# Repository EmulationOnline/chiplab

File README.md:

# Chiplab by EmulationOnline

The Chiplab is a research platform for studying the behavior of (initially just digital)
integrated circuits. 

More information about motivation & history can be found at:

https://emulationonline.com/systems/chiplab

## Structure

The long term vision is that there will be significant reuse or at least
similarity across chips, so this project is structured as a monorepo.

For a given chip supported in the lab, there are several relevant pieces:
- target. Programs meant to run on the microcontroller.
- firmware. This code runs on a microcontroller and interfaces with the 
target IC. Its core functionality is to set and read the pins
on the target IC.
- host. This is code that runs on a more powerful machine, and communicates
with the firmware program over serial.
- board. This is the electronics design for a board containing the
microcontroller, the target IC, and a serial interface for communicating
with the host.

For the 6502 chip, for example, code lives in the following folders:
- 6502/target
- 6502/firmware
- 6502/host
- 6502/board

## Contributing

If you see an issue, feel free to either open a Github issue. Please open an
issue before sending a pull request, so we can discuss. This helps make sure
we're on the same page and reduce time to implement fixes.

If you would like to see a new chip covered, feel free to open an issue. Since
supporting a chip requires several pieces, a good way to achieve this is to
build a prototype yourself by forking the 6502 code, and sending a pull request
once things are working.

## Consider donating

Donations are a great way of contributing. Funds are used both to fund
development and to acquire the hardware to add to the lab.

https://ko-fi.com/emulationonline

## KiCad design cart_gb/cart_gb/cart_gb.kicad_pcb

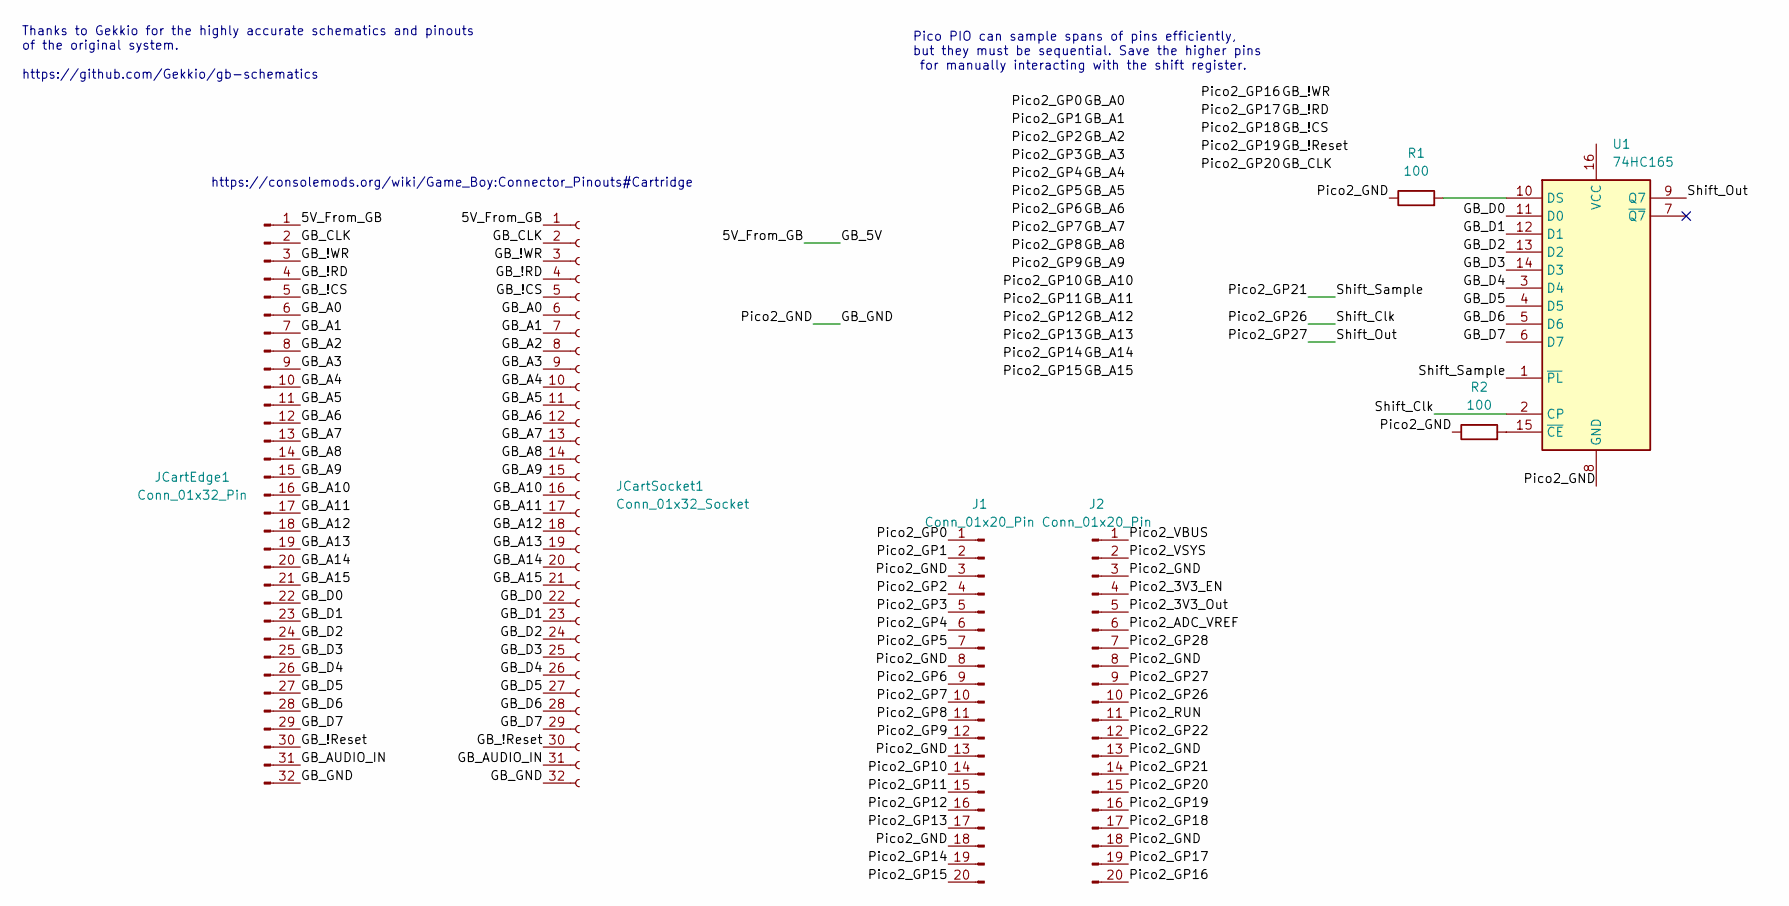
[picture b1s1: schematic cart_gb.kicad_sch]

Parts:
J1, J2: Conn_01x20_Pin; PinHeader_1x20_P2.54mm_Vertical
JCartEdge1: Conn_01x32_Pin; GameBoy_GamePak_DMG-09_P1.50mm_Edge
JCartSocket1: Conn_01x32_Socket; GameBoy_Cartridge_DMG_1x32_P1.50mm_Socket_Horizontal
R1, R2: 100; R_Axial_DIN0204_L3.6mm_D1.6mm_P1.90mm_Vertical
U1: 74HC165; DIP-16_W7.62mm_Socket

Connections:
/5V_From_GB: JCartEdge1.1, JCartSocket1.1
/GB_!CS: J2.17, JCartEdge1.5, JCartSocket1.5
/GB_!RD: J2.19, JCartEdge1.4, JCartSocket1.4
/GB_!Reset: J2.16, JCartEdge1.30, JCartSocket1.30
/GB_!WR: J2.20, JCartEdge1.3, JCartSocket1.3
/GB_A0: J1.1, JCartEdge1.6, JCartSocket1.6
/GB_A1: J1.2, JCartEdge1.7, JCartSocket1.7
/GB_A2: J1.4, JCartEdge1.8, JCartSocket1.8
/GB_A3: J1.5, JCartEdge1.9, JCartSocket1.9
/GB_A4: J1.6, JCartEdge1.10, JCartSocket1.10
/GB_A5: J1.7, JCartEdge1.11, JCartSocket1.11
/GB_A6: J1.9, JCartEdge1.12, JCartSocket1.12
/GB_A7: J1.10, JCartEdge1.13, JCartSocket1.13
/GB_A8: J1.11, JCartEdge1.14, JCartSocket1.14
/GB_A9: J1.12, JCartEdge1.15, JCartSocket1.15
/GB_A10: J1.14, JCartEdge1.16, JCartSocket1.16
/GB_A11: J1.15, JCartEdge1.17, JCartSocket1.17
/GB_A12: J1.16, JCartEdge1.18, JCartSocket1.18
/GB_A13: J1.17, JCartEdge1.19, JCartSocket1.19
/GB_A14: J1.19, JCartEdge1.20, JCartSocket1.20
/GB_A15: J1.20, JCartEdge1.21, JCartSocket1.21
/GB_AUDIO_IN: JCartEdge1.31, JCartSocket1.31
/GB_CLK: J2.15, JCartEdge1.2, JCartSocket1.2
/GB_D0: JCartEdge1.22, JCartSocket1.22, U1.11 (D0)
/GB_D1: JCartEdge1.23, JCartSocket1.23, U1.12 (D1)
/GB_D2: JCartEdge1.24, JCartSocket1.24, U1.13 (D2)
/GB_D3: JCartEdge1.25, JCartSocket1.25, U1.14 (D3)
/GB_D4: JCartEdge1.26, JCartSocket1.26, U1.3 (D4)
/GB_D5: JCartEdge1.27, JCartSocket1.27, U1.4 (D5)
/GB_D6: JCartEdge1.28, JCartSocket1.28, U1.5 (D6)
/GB_D7: JCartEdge1.29, JCartSocket1.29, U1.6 (D7)
/GB_GND: J1.3, J1.8, J1.13, J1.18, J2.3, J2.8, J2.13, J2.18, JCartEdge1.32, JCartSocket1.32, R1.1, R2.1, U1.8 (GND)
/Pico2_3V3_EN: J2.4
/Pico2_3V3_Out: J2.5
/Pico2_ADC_VREF: J2.6
/Pico2_GP21: J2.14, U1.1 (~PL)
/Pico2_GP22: J2.12
/Pico2_GP26: J2.10, U1.2 (CP)
/Pico2_GP27: J2.9, U1.9 (Q7)
/Pico2_GP28: J2.7
/Pico2_RUN: J2.11
/Pico2_VBUS: J2.1
/Pico2_VSYS: J2.2
unnamed: R1.2, U1.10 (DS)
unnamed: R2.2, U1.15 (~CE)

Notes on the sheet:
https://consolemods.org/wiki/Game_Boy:Connector_Pinouts#Cartridge
Thanks to Gekkio for the highly accurate schematics and pinouts of the original system. https://github.com/Gekkio/gb-schematics
Pico PIO can sample spans of pins efficiently, but they must be sequential. Save the higher pins for manually interacting with the shift register.

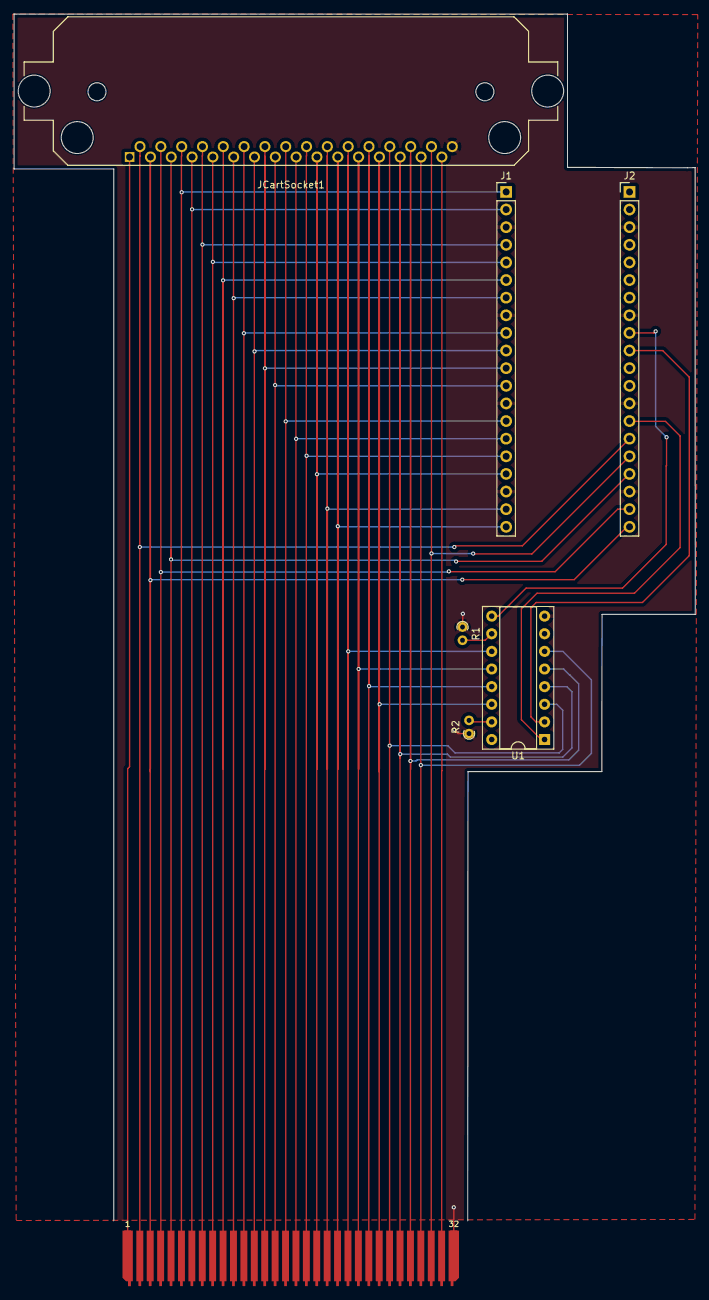
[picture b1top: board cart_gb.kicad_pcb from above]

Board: 2 copper layers, 98.2 x 173.9 mm, 7 parts (0 on the bottom side), 37 nets.

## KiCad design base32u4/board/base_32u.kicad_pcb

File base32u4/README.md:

# Base controller board

This is a barebones design for a microcontroller board based around the atmega32u4
microcontroller. This serves as a starting point for designs that support specific
digital ICs.

Designed in KiCad.

## Key features
- Powered via usb (5V)
- 3.3V used for IO
- external clock, enabling the chip to run at 16mhz
- supports serial communication over the usb connector.

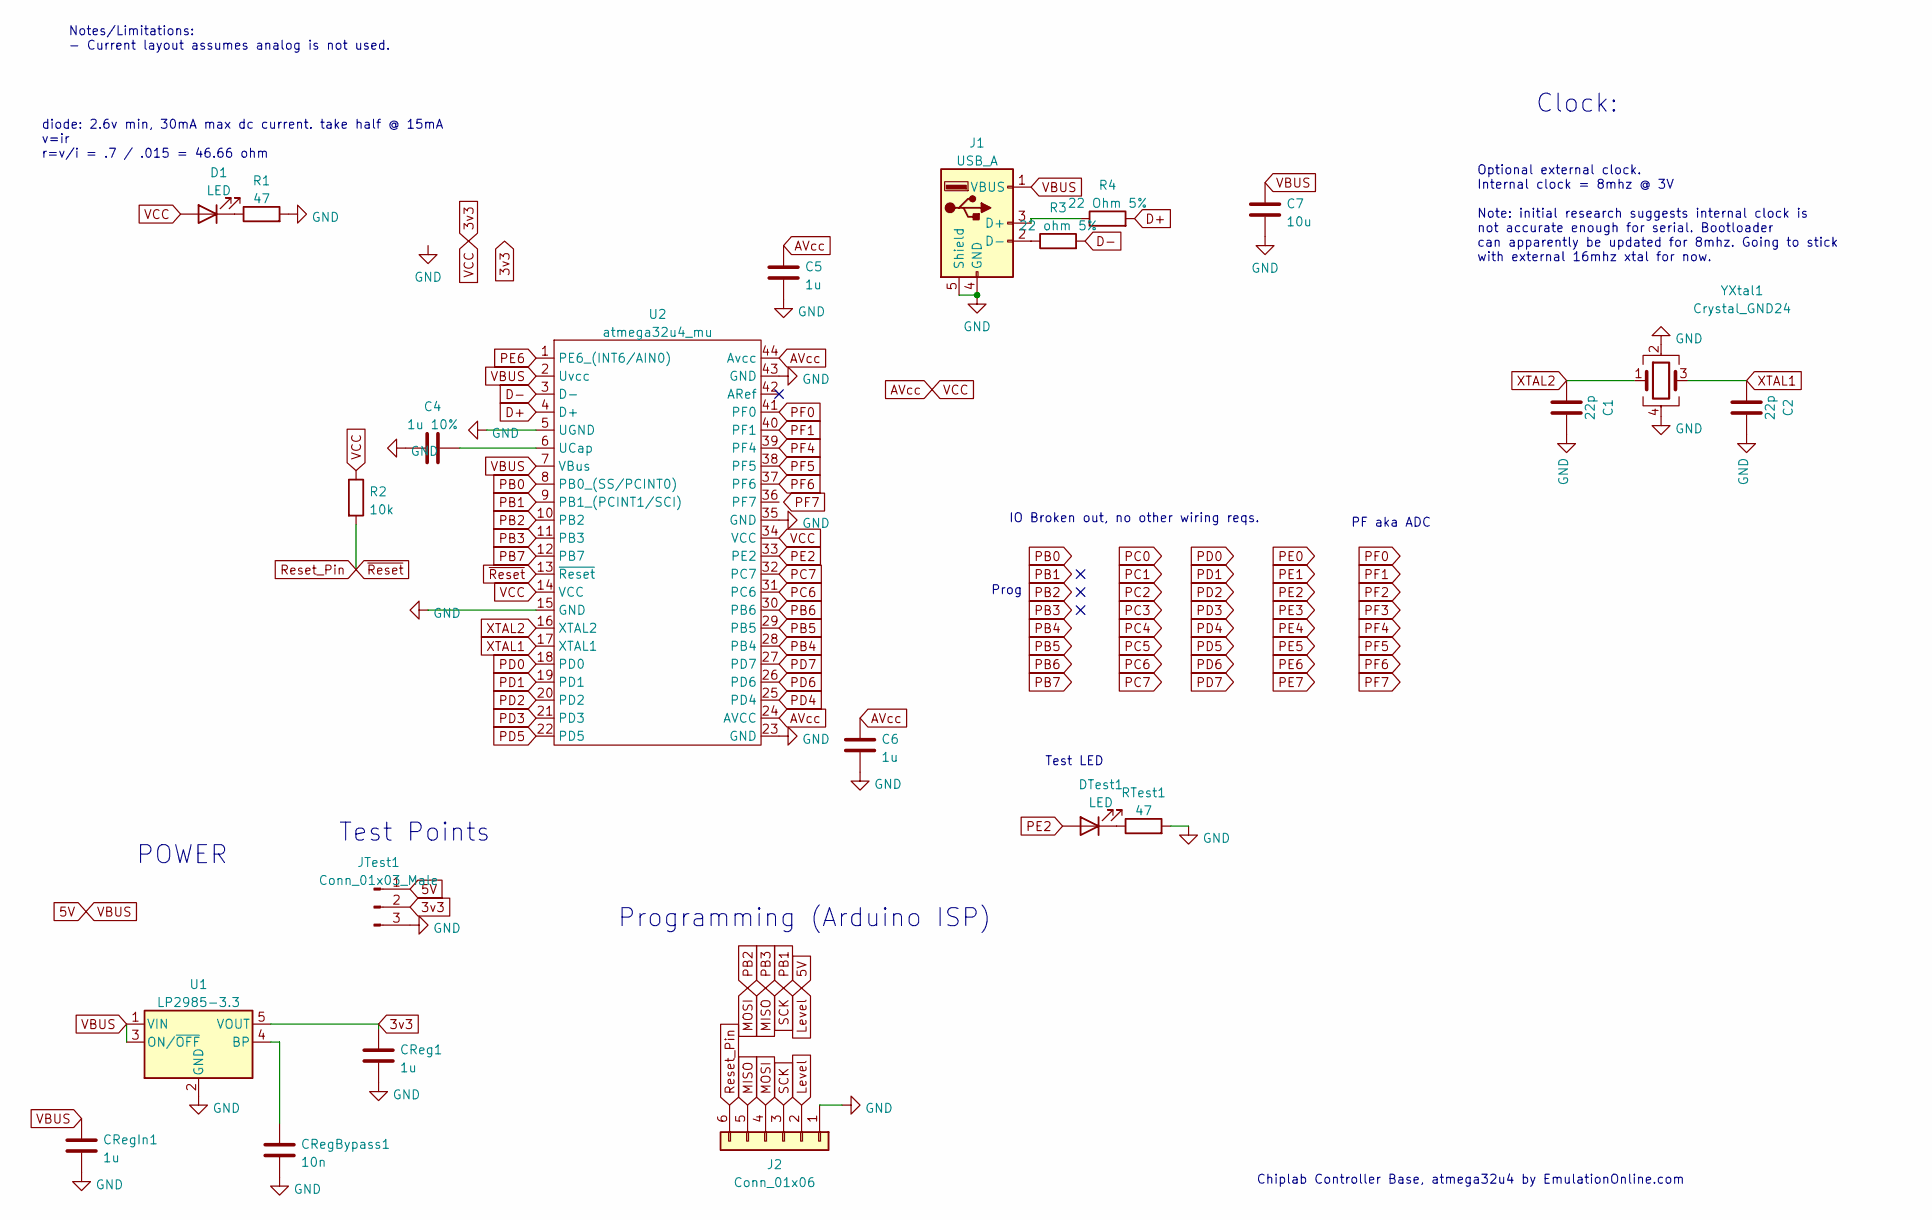
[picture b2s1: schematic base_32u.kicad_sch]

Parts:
C1, C2: 22p; C_0805_2012Metric; lcsc C123642
C4: 1u 10%; C_0805_2012Metric; lcsc C28323
C5, C6: 1u; C_0805_2012Metric; lcsc C28323
C7: 10u; C_0805_2012Metric; lcsc C15850
CReg1: 1u; C_0805_2012Metric; lcsc C28323
CRegBypass1: 10n; C_0805_2012Metric; lcsc C1710
CRegIn1: 1u; C_0805_2012Metric; lcsc C28323
D1: LED; LED_0603_1608Metric; lcsc C7496818
DTest1: LED; LED_0603_1608Metric; lcsc C7496818
J1: USB_A; USB_Micro-B_Molex_47346-0001; lcsc_old C404968
J2: Conn_01x06; PinHeader_1x06_P2.54mm_Vertical
JTest1: Conn_01x03_Male; PinHeader_1x03_P2.54mm_Vertical
R1: 47; R_0805_2012Metric; lcsc C17714
R2: 10k; R_0805_2012Metric; lcsc C17414
R3: 22 ohm 5%; R_0805_2012Metric; lcsc C17561
R4: 22 Ohm 5%; R_0805_2012Metric; lcsc C17561
RTest1: 47; R_0805_2012Metric; lcsc C17714
U1: LP2985-3.3; SOT-23-5; lcsc C95414
U2: atmega32u4_mu; QFN-44-1EP_7x7mm_P0.5mm_EP5.2x5.2mm; lcsc C112161
YXtal1: Crystal_GND24; Crystal_SMD_3225-4Pin_3.2x2.5mm; lcsc C2842190

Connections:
5V: C7.1, CRegIn1.1, J1.1 (VBUS), J2.2, JTest1.1, U1.1 (VIN), U1.3 (ON/~OFF), U2.2 (Uvcc), U2.7 (VBus)
AVcc: C5.1, C6.1, CReg1.1, D1.2 (A), JTest1.2, R2.1, U1.5 (VOUT), U2.14 (VCC), U2.24 (AVCC), U2.34 (VCC), U2.44 (Avcc)
D+: R4.2, U2.4 (D+)
D-: R3.2, U2.3 (D-)
GND: C1.2, C2.2, C4.1, C5.2, C6.2, C7.2, CReg1.2, CRegBypass1.2, CRegIn1.2, J1.4 (GND), J1.5 (Shield), J2.1, JTest1.3, R1.2, RTest1.2, U1.2 (GND), U2.5 (UGND), U2.15 (GND), U2.23 (GND), U2.35 (GND), U2.43 (GND), YXtal1.2, YXtal1.4
MISO: J2.5, U2.11 (PB3)
MOSI: J2.4, U2.10 (PB2)
unnamed: C4.2, U2.6 (UCap)
unnamed: CRegBypass1.1, U1.4 (BP)
unnamed: D1.1 (K), R1.1
unnamed: DTest1.1 (K), RTest1.1
unnamed: J1.2 (D-), R3.1
unnamed: J1.3 (D+), R4.1
PB0: U2.8 (PB0_(SS/PCINT0))
PB4: U2.28 (PB4)
PB5: U2.29 (PB5)
PB6: U2.30 (PB6)
PB7: U2.12 (PB7)
PC6: U2.31 (PC6)
PC7: U2.32 (PC7)
PD0: U2.18 (PD0)
PD1: U2.19 (PD1)
PD2: U2.20 (PD2)
PD3: U2.21 (PD3)
PD4: U2.25 (PD4)
PD5: U2.22 (PD5)
PD6: U2.26 (PD6)
PD7: U2.27 (PD7)
PE2: DTest1.2 (A), U2.33 (PE2)
PE6: U2.1 (PE6_(INT6/AIN0))
PF0: U2.41 (PF0)
PF1: U2.40 (PF1)
PF4: U2.39 (PF4)
PF5: U2.38 (PF5)
PF6: U2.37 (PF6)
SCK: J2.3, U2.9 (PB1_(PCINT1/SCI))
XTAL1: C2.1, U2.17 (XTAL1), YXtal1.3
XTAL2: C1.1, U2.16 (XTAL2), YXtal1.1
~Reset: J2.6, R2.2, U2.13 (~Reset)

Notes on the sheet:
Prog
IO Broken out, no other wiring reqs.
Test LED
Test Points
PF aka ADC
Notes/Limitations: - Current layout assumes analog is not used.
POWER
Optional external clock. Internal clock = 8mhz @ 3V Note: initial research suggests internal clock is not accurate enough for serial. Bootloader can apparently be updated for 8mhz. Going to stick with external 16mhz xtal for now.
Chiplab Controller Base, atmega32u4 by EmulationOnline.com
Programming (Arduino ISP)
Clock:
diode: 2.6v min, 30mA max dc current. take half @ 15mA v=ir r=v/i = .7 / .015 = 46.66 ohm

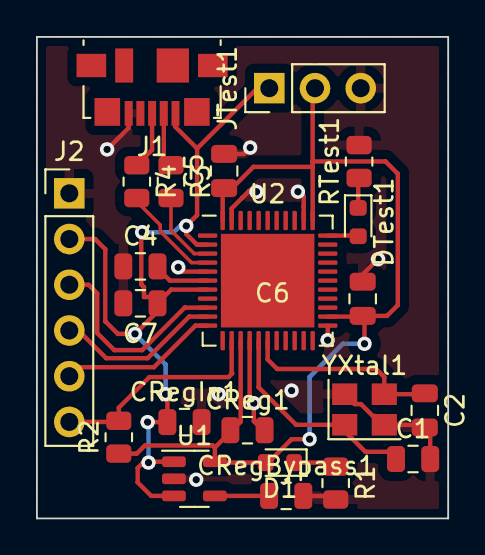
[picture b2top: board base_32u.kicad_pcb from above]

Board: 2 copper layers, 22.8 x 26.8 mm, 22 parts (0 on the bottom side), 18 nets.

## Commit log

2024-08-15 initial commit + 6502 code
2024-08-15 6502: add board placeholder.
2024-08-15 Add license.
2024-08-23 Add base controller board.
    This design should serve as a starting point when designing
    boards to interface with specific digital ICs.
    I've ordered had a few of these, and confirmed that I can flash
    the chip. Everything appears to be working.
2024-08-31 Add the modified Arduino-as-ISP sketch.
    The original sketch wouldn't program my custom boards without
    modifications. These changes include using more common programming pins,
    and programming at a lower speed to enable automatic reset.
    I've detailed the usage of this sketch on my site at:
    https://emulationonline.com/systems/chiplab/flashing-arduino-bootloader/
2024-09-03 driver -> firmware.
    Though the "driver" board conceptually drives the target IC, this
    naming is a bit misleading as a driver is typically code running on
    a host to interact with some embedded hardware.
    "Firmware" refers to code running on the embedded hardware with
    less confusion.
2024-09-08 Fork breadboard 6502 firmware for PCB board.
    Pins are different on the PCB vs the breadboard prototype. This
    also reworks the serial reading code for speed.
2024-09-08 Performance updates for 6502_pcb firmware.
    Avoid chr* -> string copy
    Increase serial frequency (9200 -> 15200)
    Decrease shift register period (10000us -> 10us)
    Datasheet for shift register indicates a hold period of about 150ns or
    .15 us at 2V
    3.3V isn't explicitly included. Arduino wait is accurate above 3us,
2024-09-08 Apply optimizations from 6502_pcb to breadboard.
    This speeds up runtime for the 6502 firmware that runs on the breadboard
    setup.
    200 cycles completed in 2.2s
2024-09-16 Support mutating memory.
2024-09-16 File permissions update.
2024-09-17 Fix memory mutability in serial_rom.
2024-09-17 Avoid problematic pins on micro.
    {tx/rx}led pins flicker due to serial activity, and cannot be used as general
    io.
    Tested this build on a breadboard with a micro.
2024-09-18 Swap 6502 pins CLK and RESET.
    The board was easier to route this way.
2025-01-20 Outline FPGA chiplab, add counter HDL demo.
    The FPGA based chiplab is new hardware designed for testing chips
    which need to be toggled at higher speeds (ex: non-static NMOS based
    chips).
    The counter demo is simple HDL is meant to help test FPGA bringup. It
    exports a 3 bit counter that should advance about once per second.
    This also includes verilator based models, which allow testing a
2025-01-23 Start fpga based 6502 chiplab HDL.
    This project is meant to be compatible with the original
    atmega based 6502 chiplab board. Using an FPGA allows the design
    to scale to faster clock speeds, as is needed for several NMOS chips.
    This commit outlines the project and adds a basic divide-by-two
    clock divider.
2025-01-24 Clock divider: Take divisor as input instead of parameter.
    Verilator doesn't allow changing parameters at runtime. This makes
    testing challenging. Instead allow each divider to be configured during
    reset.
2025-01-26 Basic outline for 6502_driver.
2025-01-26 Modify hello_fpga example for icesugar-nano
    Changing the led pin from ALWAYS_PIN to
    one of the CTR pins can make the LED constant, or blink at
    various speeds.
    Tested both LED as ALWAYS and CTR0 on the icesugar-nano.
2025-01-31 Add FPGA Pintest
    This design turns on each of the pins of the board, one at a time. This
    is useful for confirming functionality of the GPIO pins on a board.
2025-02-06 FPGA: Add echo_ram, which reads bytes then responds.
    This test reads a large sequence of bytes then returns the same message.
    This was intended as a test of the block ram module within the ice40.
    Using registers directly was simpler to implement, and still fits
    on the ice40.
    This HDL is similar to what will be needed in the chiplab. At
    the beginning of a run, memory will be copied form the host to the
2026-05-17 import libs for gb connectors.
2026-05-18 layout+route for cart_gb. sent for fab.
